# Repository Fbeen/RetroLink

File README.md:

# RetroLink

RetroLink is a small **USB input adapter for retro computers**.

It allows modern **USB mice and USB joysticks** to be used on classic systems such as:

- Atari ST
- Commodore Amiga
- Commodore 64

---

## Table of Contents

- [Features](#features)
- [Button Control & LED Feedback](#button-control--led-feedback)
- [Why This Project Exists](#why-this-project-exists)
- [How RetroLink Works](#how-retrolink-works)
  - [Microcontroller](#microcontroller-ch559l)
  - [USB Host Operation](#usb-host-operation)
  - [Mouse Emulation](#mouse-emulation)
  - [Joystick Mapping](#joystick-mapping)
  - [Open Collector Outputs](#open-collector-outputs)
  - [Serial Interface](#serial-configuration-interface)
- [Hardware](#hardware)
- [Connecting RetroLink](#connecting-retrolink)
- [Configuration Console](#opening-the-configuration-console)
- [Menu Options](#main-menu)
- [Firmware](#firmware)
- [Disclaimer](#disclaimer)

---

## Features

- USB mouse support
- USB joystick support, must be a HID joystick.
- Works with **Atari 8 bit**,  **Atari ST**, **Amiga**, and **C64**
- Configurable **mouse speed**
- Switch between **ST mouse** and **Amiga mouse**
- **Swap** left & right **mouse buttons**
- Configurable **autofire frequency**
- **Joystick learning wizard**
- Configuration stored in flash memory
- Terminal-based configuration (optional)
- Configurable with onboard button & LED

---

# Button Control & LED Feedback

## Button Overview

The RetroLink uses **one button**:

- **Short press**  Show menu on UART  
- **Long press**  Select function via LED flashes  

---

## Short Press

**< 1 second**

- Prints the **Main Menu**
- Useful when opening a serial terminal  

---

## Long Press (Selection)

| Flashes | Function |
|--------|--------|
| 1 | Controller Learning |
| 2 | Swap Mouse Mode |
| 3 | Swap Mouse Buttons |
| 4 | Increase Mouse Speed |
| 5 | Increase Autofire Speed |

Release at desired flash count

---

## Controller Learning (1 flash)

Press a key on your controller in the order below to configure it:

1. UP  
2. DOWN  
3. LEFT  
4. RIGHT  
5. FIRE  
6. AUTOFIRE  

### Feedback

- Each step **2 short flashes**
- Final step LED ON for **2 seconds**
- Config is saved automatically

### To abort the learning wizzard:

- Press **PCB button**
- Press **ESC** in terminal

---

## Mouse Mode (2 flashes)

- 1 flash Atari ST  
- 2 flashes Amiga  

---

## Mouse Buttons (3 flashes)

- 1 flash Normal  
- 2 flashes Swapped  

---

## Mouse Speed (4 flashes)

Cycles from 1 to 5 

| Flashes | Speed |
|--------|------|
| 1 | Very Slow |
| 2 | Slow |
| 3 | Normal |
| 4 | Fast |
| 5 | Turbo |

---

## Autofire Speed (5 flashes)

| Flashes | Frequency |
|--------|----------|
| 1 | 8 Hz |
| 2 | 9 Hz |
| 3 | 10 Hz |
| 4 | 11 Hz |
| 5 | 12 Hz |

---

## Notes

- Settings are stored in flash
- Persist after reboot
- LED is primary UI without UART

---

# Why This Project Exists

Classic hardware is aging:

- cables break  
- hardware wears out  
- ergonomics are outdated  

RetroLink solves this by allowing **modern USB devices** to be used.

---

# How RetroLink Works

RetroLink translates USB input into **DB9 signals**.

Internally:

- USB HID reports are read
- Converted to:
  - quadrature signals (mouse)
  - digital lines (joystick)
  - autofire pulses

---

## Microcontroller: CH559L

I chose the CH559 because it operates directly on the 5 volts from the retro computer and therefore does not require a power regulator. Furthermore, the CH559 microcontroller has a built-in USB transceiver and USB controller. The DB9 interfaces are electrically very simple, but they rely on a specific signaling method: open-collector (or open-drain) logic.

Key features for the CH559:

- 8051-based MCU
- USB Host + Device
- 5V operation and low current 3.3v output
- Built-in flash storage

### RAM Limitation

The disadvantage of the CH559 is the small RAM size. That's why strings are stored in flash using `__code`, for example:

    static const char __code text[] = "Example";

---

## USB Host Operation

Supports HID devices:

- mouse
- joystick
- gamepads

---

## Mouse Emulation

Uses quadrature encoding:

---

## Joystick Mapping

Learning wizard detects:

- changed bytes
- thresholds
- control mapping

---

## Open Collector Outputs

Uses open-drain signals:

- only pulls LOW
- host provides pull-up

---

## Serial Configuration Interface

The RX and TX UART0 lines are connected to the CH340N UART-to-USB controller. This ensures that a micro USB cable can be used for the configuration.

---

# Hardware

See the [hardware section](/hardware/readme.md).

---

# Connecting RetroLink

1. Plug into DB9 mouse or joystick port on your Atari 8 bit / ST / Amiga /C64
2. Connect HID mouse/controller to the USB-A port
3. *Optional: connect micro USB cable to your PC to use the console*
4.  For joystick emulation run the **learning wizzard** once.

---

# Opening the Configuration Console

Connect a USB cable from your pc to the micro USB port on the pcb. Any serial console could be used like:

- Arduino's serial monitor
- Visual Studio Code's serial monitor
- PuTTY
- TeraTerm
- minicom

Settings:

```
2000000 baud
8 data bits
no parity
1 stop bit
```
---

## Main Menu

---

# Firmware

See the [firmware section](/firmware.md).

---

# Repository

https://github.com/Fbeen/RetroLink

---

# Disclaimer

Provided as-is. Use at your own risk.

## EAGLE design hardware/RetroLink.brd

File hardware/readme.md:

# Hardware

The RetroLink hardware was designed in **Autodesk EAGLE**.

If you want to modify the design yourself, you can download Autodesk EAGLE for free through the **Fusion 360 Personal Use License**. This license is intended for hobbyists and non-commercial projects.

Useful links:

https://www.autodesk.com/products/fusion-360/personal  
https://www.autodesk.com/products/eagle/overview  

The free version has a few limitations, but for small hobby projects like this it works perfectly fine:

- Maximum **2 schematic sheets**
- Maximum **2 signal layers**
- Maximum **100 cm² PCB area**

---

# Ordering the PCB at JLCPCB

You can simply order it **almost fully assembled** from JLCPCB.

To make this easy, the repository already contains the required manufacturing files.

You will find them here: `hardware/jlcpcb.com/`

Inside that folder you will find:

- `CAMOutput.zip` – the Gerber files (PCB manufacturing files)
- `bom.xls` – Bill of Materials
- `cpl.xls` – Component placement file

---

## Step-by-step ordering

1. Go to https://jlcpcb.com

2. Log in or create an account.

3. Press **Order Now**

4. Upload the file: `CAMOutput.zip`

5. Choose your preferred **PCB color**

6. Enable **PCB Assembly**

7. Select the quantity  
(usually **2 or 5 boards** is the cheapest option)

8. Press **Next**

9. Press **Next** again

10. Upload the assembly files

- BOM file → `bom.xls`
- CPL file → `cpl.xls`

11. Press **Process BOM & CPL**

12. **Important:** carefully check the detected parts.

13. Press **Next**

14. Check the orientation of the following components:

- **U1** → dot at **bottom-left**
- **U2** → dot at **top-right**
- **U3** → dot at **bottom-right**
- **LED** → **left = negative**, **right = positive**

15. Press **Save to cart**

16. Place your order and complete payment.

17. Now comes the hardest part: **waiting for the package to arrive.**

---

# Adding the DB9 and USB-A connectors

The **DB9** and **USB-A** connectors are **not assembled by JLCPCB**, so you will need to solder them yourself.

Luckily this is very easy and only takes a few minutes.

You will need:

- **DB9 Connector – PCB Mount – Serial – 9 Pin – 2 Rows**
- **USB-A Connector – PCB Mount**

Example connectors:

---

# Compiling and flashing the firmware (Windows)

The **CH559L microcontroller** can be programmed directly through USB.

For this you will need a **USB-A to USB-A cable**.

---

## Compiling and flashing instructions

1. Clone the complete repository

https://github.com/Fbeen/RetroLink

or use:

```
git clone https://github.com/Fbeen/RetroLink
```

2. Open a **Command Prompt** in Windows.

3. Change to the repository directory

```
cd RetroLink
```

4. Connect the PCB to your computer using the **USB-A to USB-A cable**  
while **holding the button on the PCB**.

5. If everything goes well you should hear the familiar  
**"new USB device detected"** sound from Windows.

6. Run the build script:

```
cd scripts
compile
```

The firmware will now be compiled and flashed to the **CH559L**.

---

# Repository

The complete project can be found here:

https://github.com/Fbeen/RetroLink

Feel free to explore the project, modify the hardware or firmware, and build your own RetroLink adapter.

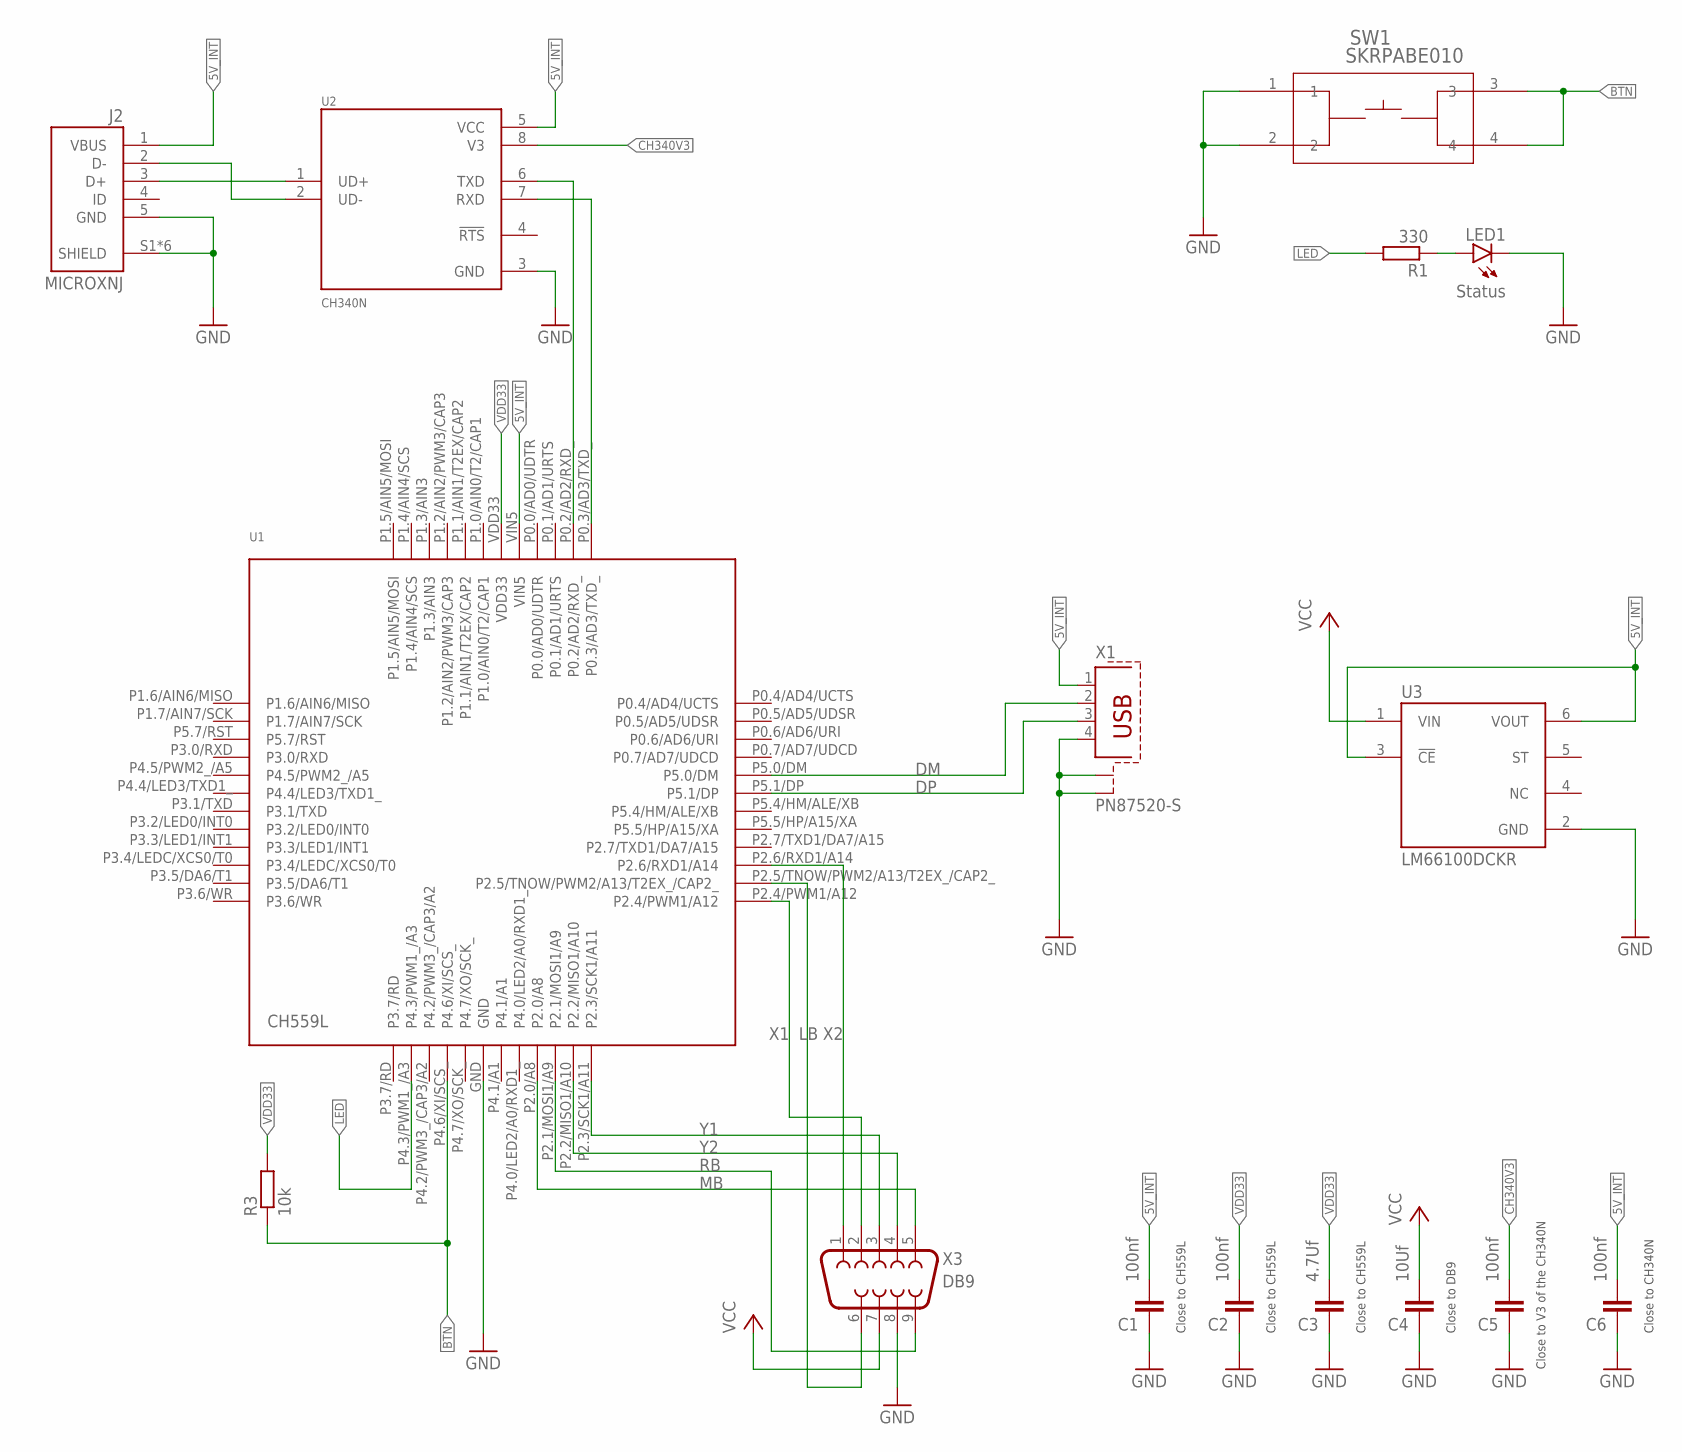
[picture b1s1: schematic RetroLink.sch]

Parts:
C1, C2, C5, C6: 100nf; C0603
C3: 4.7Uf; C0603
C4: 10Uf; C0603
J2: MICROXNJ; SHOUHAN_MICROXNJ
LED1: Status; SML0603
R1: 330; R0603
R3: 10k; R0603
SW1: SKRPABE010; SW4_SKRPABE010_ALPS
U1: CH559L; TQFP48_7X7
U2: CH340N; SOIC127P600X160-8N
U3: LM66100DCKR; SOT65P210X110-6N
X1: PN87520-S
X3: DB9; F09D

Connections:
5V_INT: C1.2, C6.2, J2.1 (VBUS), U1.VIN5, U2.5 (VCC), U3.3 (!CE), U3.6 (VOUT), X1.1
BTN: R3.1, SW1.3, SW1.4, U1.P4.6/XI/SCS_
CH340V3: C5.2, U2.8 (V3)
DM: U1.P5.0/DM, X1.2
DP: U1.P5.1/DP, X1.3
GND: C1.1, C2.1, C3.1, C4.1, C5.1, C6.1, J2.5 (GND), J2.S1 (SHIELD), J2.S2 (SHIELD), J2.S3 (SHIELD), J2.S4 (SHIELD), J2.S5 (SHIELD), J2.S6 (SHIELD), LED1.C, SW1.1, SW1.2, U1.GND, U2.3 (GND), U3.2 (GND), X1.4, X1.S1, X1.S2, X3.8
LB: U1.P2.5/TNOW/PWM2/A13/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, X3.6
LED: R1.2, U1.P4.3/PWM1_/A3
MB: U1.P2.0/A8, X3.5
unnamed: J2.2 (D-), U2.2 (UD-)
unnamed: J2.3 (D+), U2.1 (UD+)
RB: U1.P2.1/MOSI1/A9, X3.9
RXD: U1.P0.2/AD2/RXD_, U2.6 (TXD)
TXD: U1.P0.3/AD3/TXD_, U2.7 (RXD)
VCC: C4.2, U3.1 (VIN), X3.7
VDD33: C2.2, C3.2, R3.2, U1.VDD33
VLED: LED1.A, R1.1
X1: U1.P2.4/PWM1/A12, X3.2
X2: U1.P2.6/RXD1/A14, X3.1
Y1: U1.P2.3/SCK1/A11, X3.3
Y2: U1.P2.2/MISO1/A10, X3.4

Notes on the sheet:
Close to DB9
Close to CH559L
Close to CH340N
Close to V3 of the CH340N

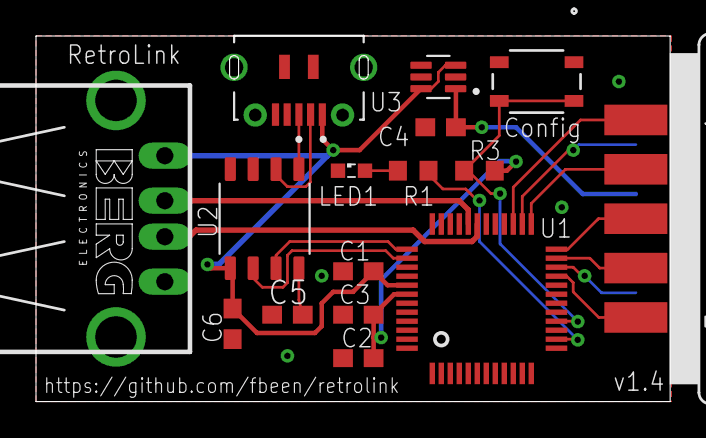
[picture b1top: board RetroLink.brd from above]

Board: 2 copper layers, 35.2 x 20.3 mm, 16 parts (0 on the bottom side), 21 nets.

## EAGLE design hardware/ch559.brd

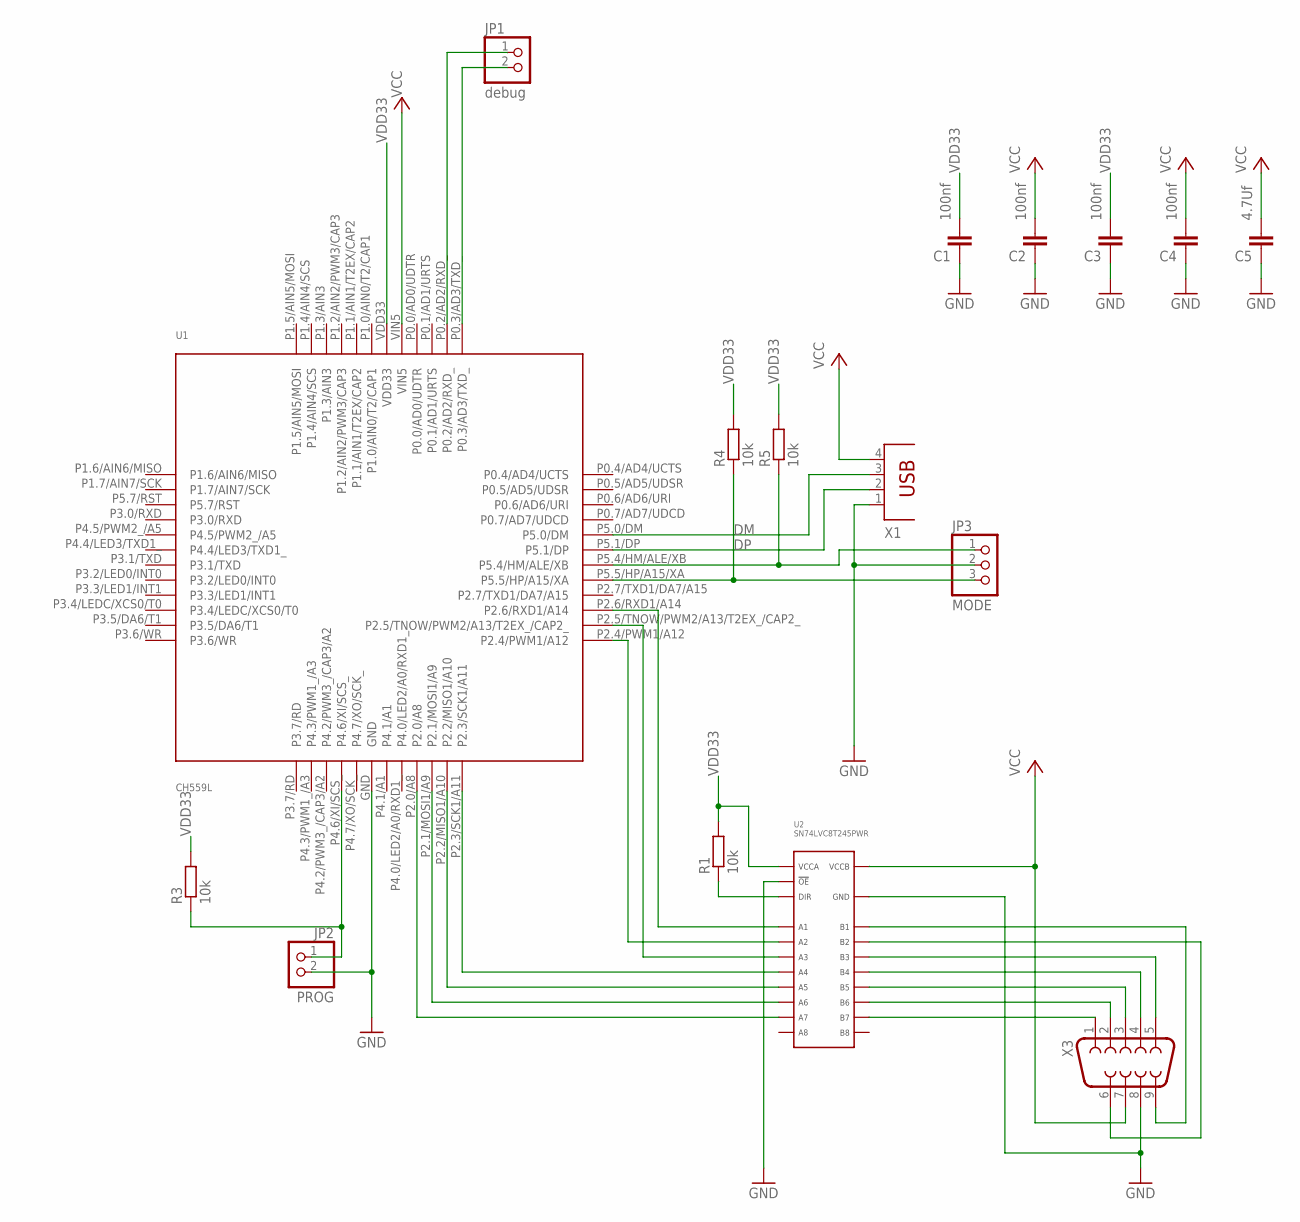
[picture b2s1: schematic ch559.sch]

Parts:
C1, C2, C3, C4: 100nf; C0603
C5: 4.7Uf; C0603
JP1: debug; 1X02
JP2: PROG; 1X02
JP3: MODE; 1X03
R1, R3, R4, R5: 10k; R0603
U1: CH559L; TQFP48_7X7
U2: SN74LVC8T245PWR; TTSOP-24
X1: PN87520
X3: F09D

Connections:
DM: U1.P5.0/DM, X1.3
DP: U1.P5.1/DP, X1.2
GND: C1.1, C2.1, C3.1, C4.1, C5.1, JP2.2, JP3.2, U1.GND, U2.P$11 (GND), U2.P$12 (GND), U2.P$13 (GND), U2.P$22 (!OE), X1.1, X3.8
LB: U2.P$17 (B5), X3.3
unnamed: U2.P$15 (B7), X3.1
unnamed: U2.P$20 (B2), X3.6
unnamed: U2.P$21 (B1), X3.9
unnamed: JP3.1, R5.1, U1.P5.4/HM/ALE/XB
unnamed: JP3.3, R4.1, U1.P5.5/HP/A15/XA
unnamed: R1.1, U2.P$2 (DIR)
P2.0: U1.P2.0/A8, U2.P$9 (A7)
P2.1: U1.P2.1/MOSI1/A9, U2.P$8 (A6)
P2.2: U1.P2.2/MISO1/A10, U2.P$7 (A5)
P2.3: U1.P2.3/SCK1/A11, U2.P$6 (A4)
P2.4: U1.P2.4/PWM1/A12, U2.P$4 (A2)
P2.5: U1.P2.5/TNOW/PWM2/A13/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, U2.P$5 (A3)
P2.6: U1.P2.6/RXD1/A14, U2.P$3 (A1)
PROG: JP2.1, R3.1, U1.P4.6/XI/SCS_
RB: U2.P$16 (B6), X3.2
RXD: JP1.1, U1.P0.2/AD2/RXD_
TXD: JP1.2, U1.P0.3/AD3/TXD_
VCC: C2.2, C4.2, C5.2, U1.VIN5, U2.P$23 (VCCB), U2.P$24 (VCCB), X1.4, X3.7
VDD33: C1.2, C3.2, R1.2, R3.2, R4.2, R5.2, U1.VDD33, U2.P$1 (VCCA)
Y1: U2.P$19 (B3), X3.5
Y2: U2.P$18 (B4), X3.4

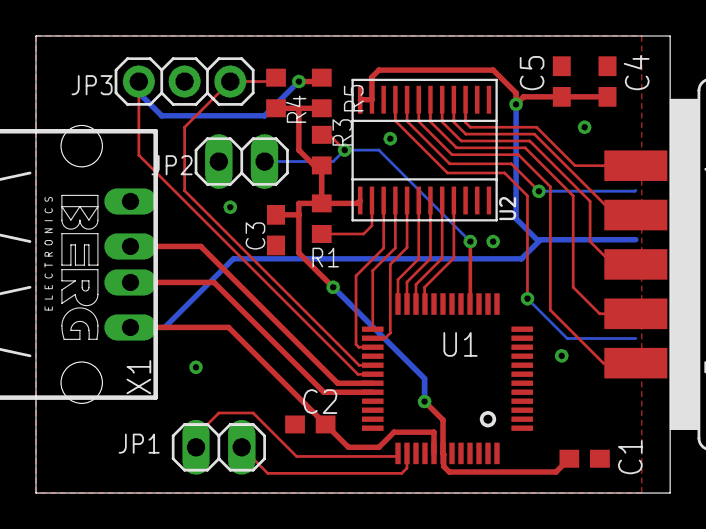
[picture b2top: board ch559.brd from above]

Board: 2 copper layers, 35.2 x 25.4 mm, 16 parts (0 on the bottom side), 25 nets.

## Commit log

2026-03-13 added joystick support
2026-03-14 userfriendly joystick learner
2026-03-15 optimimized config and no defautl joystick
2026-03-15 Amiga mouse added
2026-03-17 hardware and readme
2026-03-17 resized image minimal changes readme
2026-03-19 extended readme
2026-03-19 image url changed
2026-03-19 header image added
2026-04-01 new hardware version
2026-04-08 led and pushbutton
2026-04-08 led connection
2026-04-08 Add RetroLink image to hardware readme
    Added an image of RetroLink and updated the readme.
2026-04-09 hardware version 3, lots of comments
2026-04-09 deleted temp files
2026-04-09 hardware changes
2026-05-03 image header
2026-05-03 readme
2026-05-03 readme link

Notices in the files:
parts and their libraries:
COPYRIGHT: Copyright (C) 2026 Ultra Librarian. All rights reserved.
